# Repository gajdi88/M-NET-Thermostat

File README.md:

# M-NET-Thermostat
Smart thermostat for Mitsubishi's M-NET communication protocol

Massive thanks to Len Shustek for figuring out the protocol. This project largely builds on his work at https://github.com/LenShustek/M-NET-Sniffer

Project bundles a simulation of the M-NET to Serial converter - including conversion to 3.3V TTL logic in preparation for a Raspberry Pi to interpret the signals.

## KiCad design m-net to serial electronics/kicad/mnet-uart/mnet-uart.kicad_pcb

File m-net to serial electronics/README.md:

# M-NET to Serial adapter

Since M-NET relies on a proprietary protocol, some custom electronics are required to be able to read and write to the bus. This is to simulate the behaviour of the comms protocol in designing the electronics.

The falstad schematic can be loaded into a free circuit simluator at https://www.falstad.com/circuit/circuitjs.html

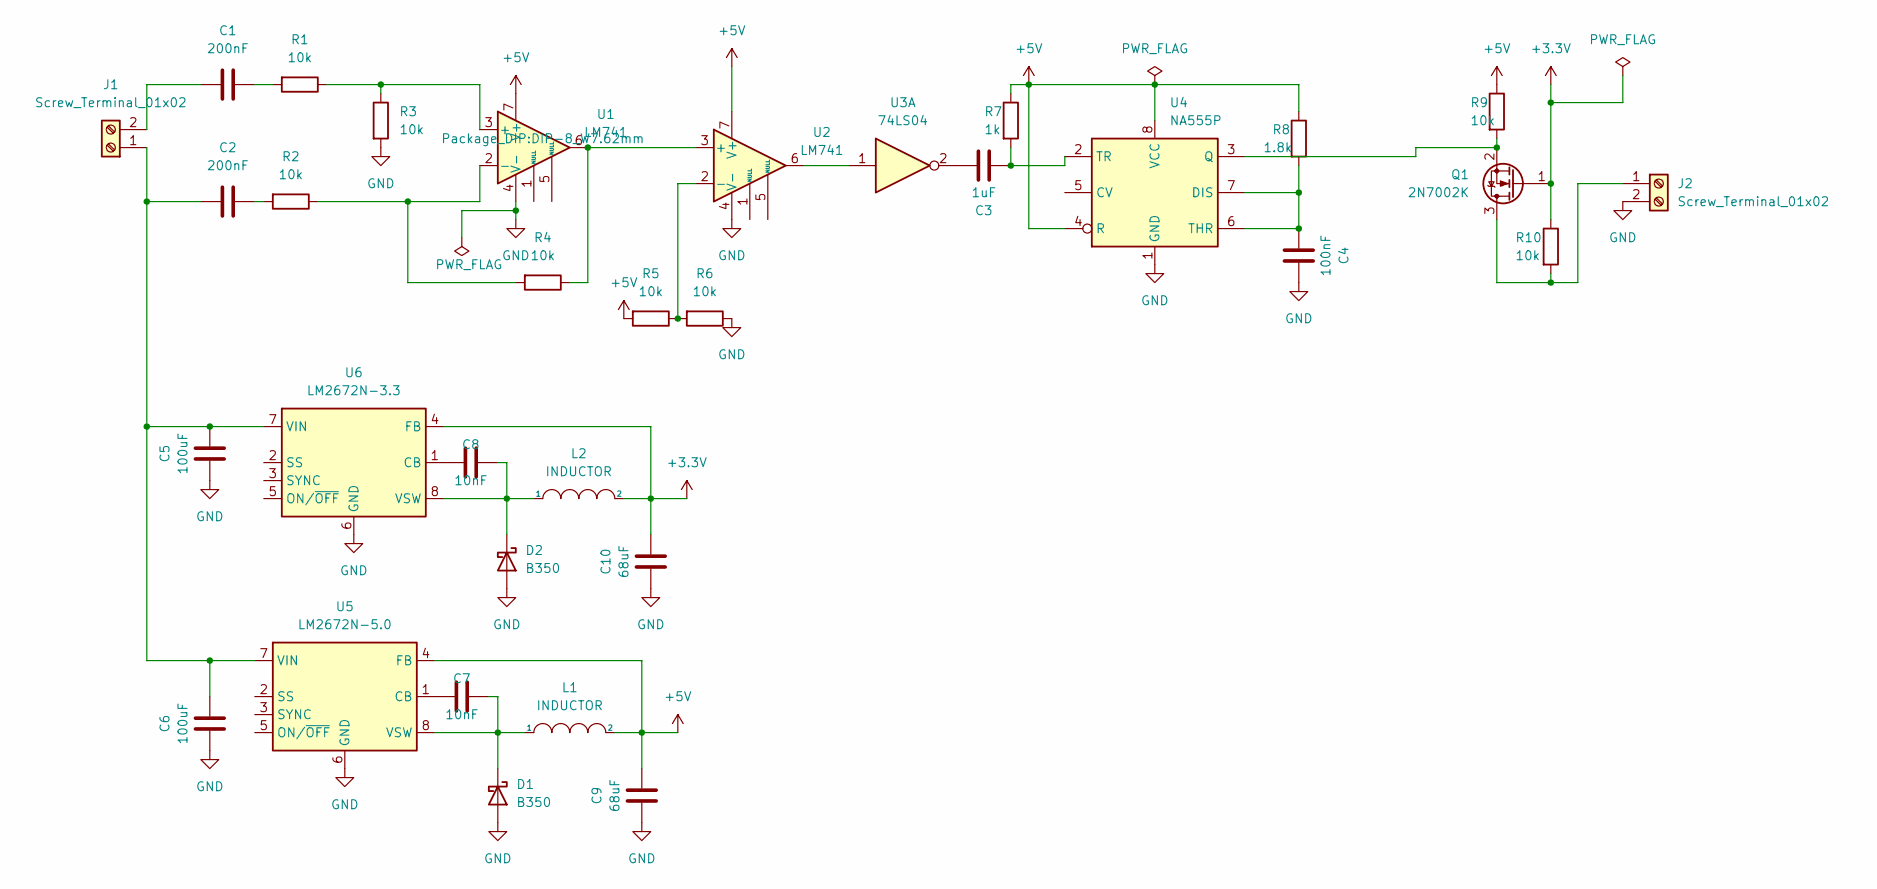
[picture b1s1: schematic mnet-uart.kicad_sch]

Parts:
C1, C2: 200nF; C_0805_2012Metric
C3: 1uF; C_0805_2012Metric
C4: 100nF; C_0805_2012Metric
C5, C6: 100uF; C_0805_2012Metric
C7, C8: 10nF; C_0805_2012Metric
C9, C10: 68uF; C_0805_2012Metric
D1, D2: B350; D_SMC
J1, J2: Screw_Terminal_01x02; TerminalBlock_Phoenix_MKDS-1,5-2-5.08_1x02_P5.08mm_Horizont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
L1, L2: INDUCTOR; L_Axial_L6.6mm_D2.7mm_P10.16mm_Horizontal_Vishay_IM-2
Q1: 2N7002K; SOT-23
R1, R2, R3, R4, R5, R6, R9, R10: 10k; R_0805_2012Metric
R7: 1k; R_0805_2012Metric
R8: 1.8k; R_0805_2012Metric
U1, U2: LM741; DIP-8_W7.62mm
U3: 74LS04; DIP-14_W7.62mm
U4: NA555P; DIP-8_W7.62mm
U5: LM2672N-5.0; DIP-8_W7.62mm
U6: LM2672N-3.3; DIP-8_W7.62mm

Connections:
+3.3V: C10.1, L2.2, Q1.1 (G), R10.1, U6.4 (FB)
+5V: C9.1, L1.2, R5.2, R7.1, R8.1, R9.1, U1.7 (V+), U2.7 (V+), U4.4 (R), U4.8 (VCC), U5.4 (FB)
GND: C4.1, C5.2, C6.2, C9.2, C10.2, D1.2 (A), D2.2 (A), J2.2, R3.2, R6.1, U1.4 (V-), U2.4 (V-), U4.1 (GND), U5.6 (GND), U6.6 (GND)
unnamed: C1.1, J1.2
unnamed: C1.2, R1.2
unnamed: C2.1, R2.2
unnamed: C2.2, C5.1, C6.1, J1.1, U5.7 (VIN), U6.7 (VIN)
unnamed: C3.1, U3.2
unnamed: C3.2, R7.2, U4.2 (TR)
unnamed: C4.2, R8.2, U4.6 (THR), U4.7 (DIS)
unnamed: C7.1, U5.1 (CB)
unnamed: C7.2, D1.1 (K), L1.1, U5.8 (VSW)
unnamed: C8.1, U6.1 (CB)
unnamed: C8.2, D2.1 (K), L2.1, U6.8 (VSW)
unnamed: J2.1, Q1.3 (D), R10.2
unnamed: Q1.2 (S), R9.2, U4.3 (Q)
unnamed: R1.1, R3.1, U1.3 (+)
unnamed: R2.1, R4.2, U1.2 (-)
unnamed: R4.1, U1.6, U2.3 (+)
unnamed: R5.1, R6.2, U2.2 (-)
unnamed: U2.6, U3.1

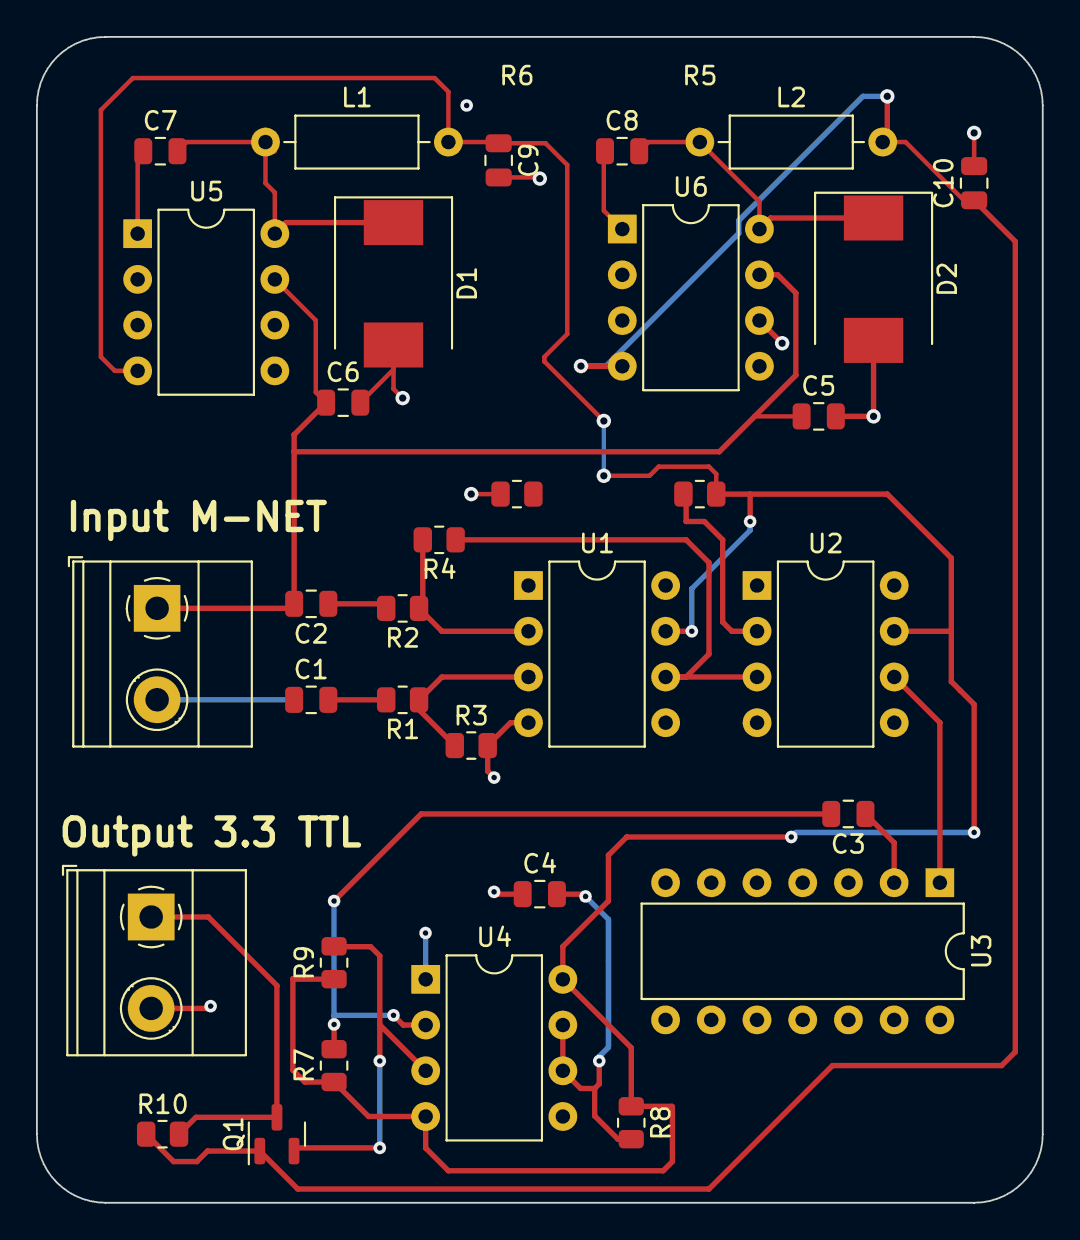
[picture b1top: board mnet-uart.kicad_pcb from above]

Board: 2 copper layers, 55.9 x 64.8 mm, 33 parts (0 on the bottom side), 21 nets.

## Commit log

2024-01-04 First version of simulating the M-NET circuit to serial converter
2024-01-04 added comments on schematic
2024-01-04 comments
2024-01-04 added monostable multivib
2024-01-04 added 555 based monostable multivibrator
2024-01-04 Added comments
2024-01-04 Labelled scopes
2024-01-04 Added comments on high pass filter
2024-01-04 comments on opamps
2024-01-04 Converted to 3.3V logic so that RPI and ESP8266 can read the UART serial comms
2024-01-04 5V supply op amps
2024-01-04 Significantly simplified TTL conversion
2024-01-04 switched to real IC741 opamps
2024-01-04 ignore pdfs
2024-01-04 cleanup
2024-01-04 kicad schematics
2024-01-04 kicad schematics draft1
2024-01-04 Schematics and layout updates
2024-01-04 minor
2024-01-05 added power supply
2024-07-18 added code for python sniffer
2024-07-21 Added diode clampdown to 0v to 5v
    note: too high current
2024-07-21 Added current limiting resistor
2024-07-21 cleanup and notes
2026-02-22 Shustek's schematic
2026-02-22 more accurate pulse inputs
2026-02-22 data inputs for circuit sim
